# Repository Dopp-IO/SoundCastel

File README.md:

# SoundCastel
Tiny castellated USB sound card and stereo amplifier

Part	Value	Package  
C1		8pF		0402  
C2		8pF		0402  
C3		1uF		0402  
C4		1uF		0402  
C5		10uF	0402  
C6		1uF		0402  
C7		1uF		0402  
C8		1uF		0402  
C9		1uF		0402  
C10		0.1uF	0402  
C11		10uF	0402  
C12		1uF		0402  
C13		0.1uF	0402  
R1		1M		0402  
R2		1.5K	0402  
R3		1.5K	0402  
U1		PCM2704C  
U2		MAX98306  
X1		ABM10

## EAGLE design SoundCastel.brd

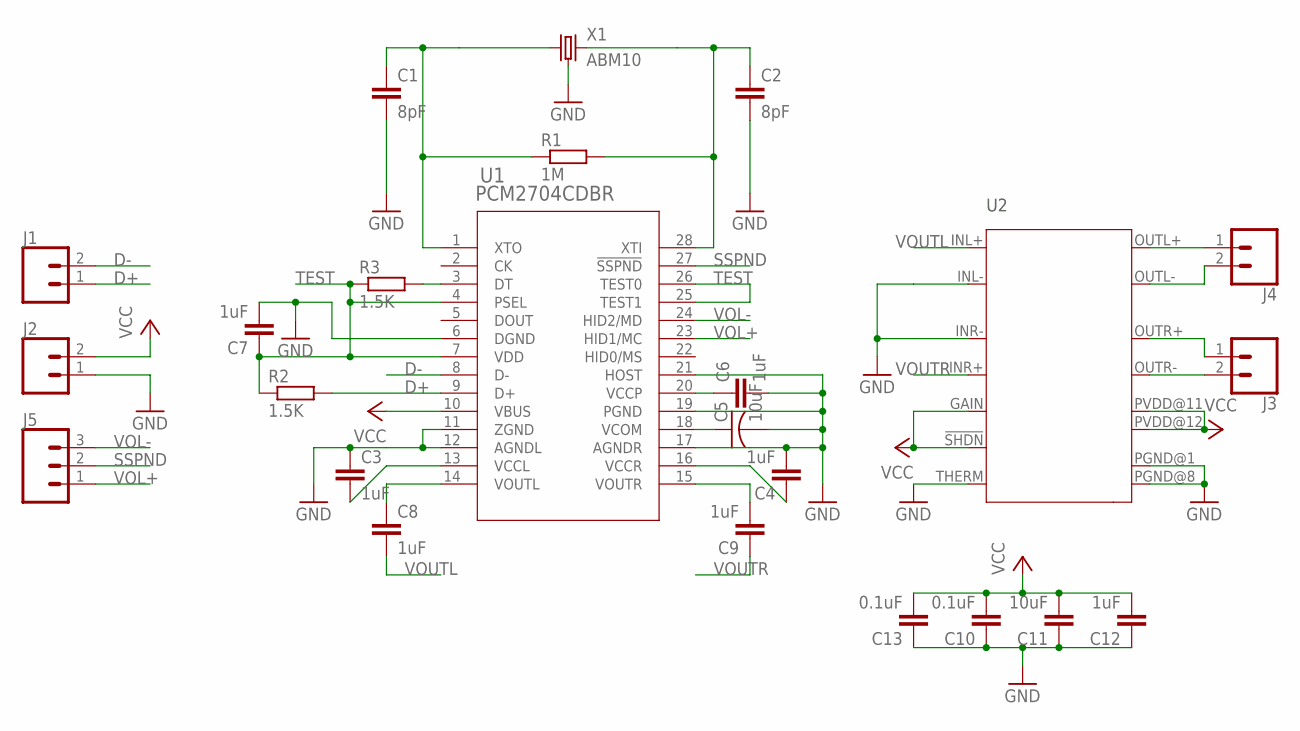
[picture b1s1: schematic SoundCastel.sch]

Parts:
C1, C2: 8pF; C0402
C3, C4, C6, C7, C8, C9, C12: 1uF; C0402
C5, C11: 10uF; C0402
C10, C13: 0.1uF; C0402
J1, J2, J3, J4: CONN_021X02_NO_SILK; 1X02_NO_SILK
J5: CONN_031X03_NO_SILK; 1X03_NO_SILK
R1: 1M; R0402
R2, R3: 1.5K; R0402
U1: PCM2704CDBR; DB28
U2: MAX98306; TDFN14
X1: ABM10

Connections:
D+: J1.1, R2.2, U1.9 (D+)
D-: J1.2, U1.8 (D-)
GND: C1.2, C2.2, C3.1, C4.2, C5.2, C6.2, C7.2, C10.1, C11.1, C12.1, C13.1, J2.1, U1.6 (DGND), U1.11 (ZGND), U1.12 (AGNDL), U1.17 (AGNDR), U1.19 (PGND), U1.21 (HOST), U2.INL- (4), U2.INR- (7), U2.PGND@1 (1), U2.PGND@8 (8), U2.THERM (THERMAL), X1.2 (3), X1.4 (3)
unnamed: C1.1, R1.1, U1.1 (XTO), X1.1
unnamed: C2.1, R1.2, U1.28 (XTI), X1.3 (2)
unnamed: C5.1, U1.18 (VCOM)
unnamed: C6.1, U1.20 (VCCP)
unnamed: C3.2, U1.13 (VCCL)
unnamed: C4.1, U1.16 (VCCR)
unnamed: R3.2, U1.3 (DT)
OUTL+: J4.1, U2.OUTL+ (13)
OUTL-: J4.2, U2.OUTL- (14)
OUTR+: J3.1, U2.OUTR+ (10)
OUTR-: J3.2, U2.OUTR- (9)
SSPND: J5.2, U1.27 (!SSPND)
TEST: C7.1, R2.1, R3.1, U1.4 (PSEL), U1.7 (VDD), U1.25 (TEST1), U1.26 (TEST0)
VCC: C10.2, C11.2, C12.2, C13.2, J2.2, U1.10 (VBUS), U2.!SHDN (2), U2.GAIN (5), U2.PVDD@11 (11), U2.PVDD@12 (12)
VOL+: J5.1, U1.23 (HID1/MC)
VOL-: J5.3, U1.24 (HID2/MD)
VOUTL: C8.2, U2.INL+ (3)
VOUTR: C9.1, U2.INR+ (6)
XVOUTL: C8.1, U1.14 (VOUTL)
XVOUTR: C9.2, U1.15 (VOUTR)

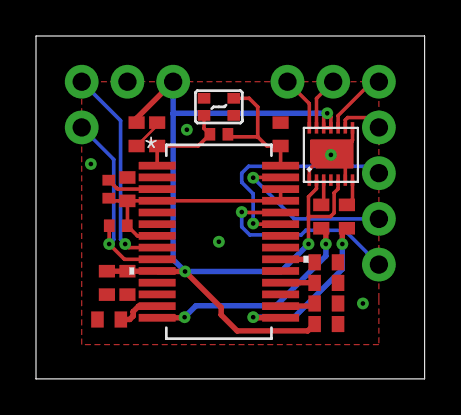
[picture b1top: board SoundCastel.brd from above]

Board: 2 copper layers, 21.6 x 19.1 mm, 24 parts (0 on the bottom side), 23 nets.

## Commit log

2018-08-11 Added gerber and source files
2018-08-11 Added BOM
2018-08-11 Added schematic PDF
2018-08-27 Fixed BOM

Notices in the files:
parts and their libraries:
SparkFun-Connectors: Licensing: Creative Commons ShareAlike 4.0 International - https://creativecommons.org/licenses/by-sa/4.0
